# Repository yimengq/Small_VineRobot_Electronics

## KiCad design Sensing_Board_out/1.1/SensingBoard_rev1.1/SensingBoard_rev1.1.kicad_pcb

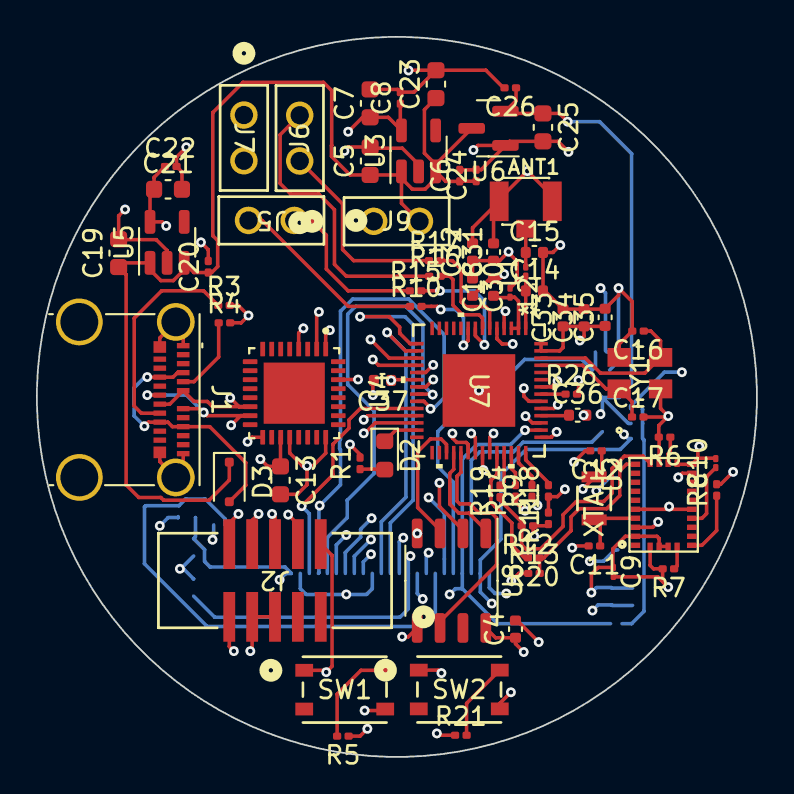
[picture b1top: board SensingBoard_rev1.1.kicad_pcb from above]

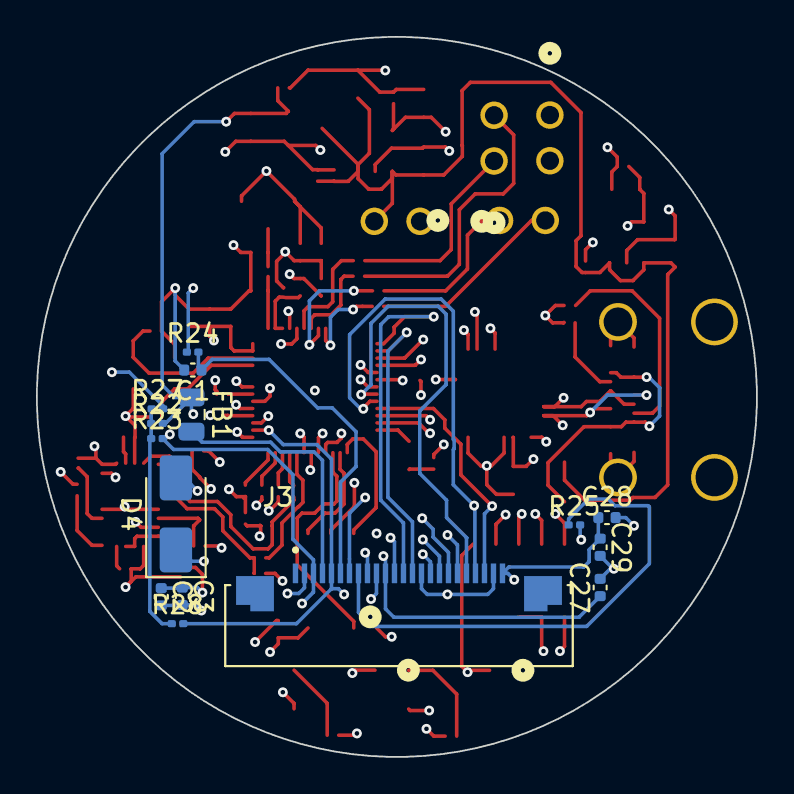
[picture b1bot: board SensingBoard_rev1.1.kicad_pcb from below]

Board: 6 copper layers, 40.0 x 40.0 mm, 89 parts (15 on the bottom side), 74 nets.

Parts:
ANT1: U.FL-R-SMT-1
C1, C2, C4, C18, C29, C30, C34, C36, C37: 100nF; C_0402_1005Metric
C3: 4.7uF; C_0402_1005Metric
C5, C7, C13, C19, C21, C23, C25: 10uF; C_0603_1608Metric
C6, C8, C20, C22, C24, C26: 1uF; C_0201_0603Metric
C9, C10: 0.1uF; C_01005_0402Metric
C11, C12: 22pF; C_0201_0603Metric
C14, C15: 1.6pF; C_0402_1005Metric
C16, C17: 18pF; C_0201_0603Metric
C27, C28, C31, C32, C33: 2.2uF; C_0402_1005Metric
C35: 10nF; C_0402_1005Metric
D2: LED; LED_0603_1608Metric
D3: PMEG6010CEJ; D_SOD-323F
D4: B140-E3; D_SMA
FB1: 120R-3A; C_0805_2012Metric
J1: USB_C_Receptacle; USB_C_Receptacle_Molex_105450-0101-L
J2: 3221-10-0300-00; CONN10_3221-10-0300-00_CNC
J3: F32R-1A7H1-11024; AMPHENOL_F32R-1A7H1-11024
J5, J6, J7, J9: RS1-02-G; CONN_RS1-02-G_ADM
L1, L2: 2nH; L_01005_0402Metric
R1: 100; R_0201_0603Metric
R3: 6.1K; R_0201_0603Metric
R4: 5.1K; R_0201_0603Metric
R5, R6, R7, R8, R11, R12, R13, R21, R24, R25: 10k; R_0201_0603Metric
R9, R10, R14, R15, R16, R17, R18, R19, R20, R22, R27: 0k; R_0201_0603Metric
R23, R28: 4.7k; R_0201_0603Metric
R26: 499; R_0201_0603Metric
SW1, SW2: PTS815 SJM 250 SMTR LFS; SW4_PTS815 SJM 250 SMTR LFS_CNK
U2: BNO055; LGA28R50P4X10_380X520X100
U3: MIC5504-3.3YM5; SOT-23-5
U4: FT232RQ; QFN50P500X500X90-33N
U5: MIC5504-1.8YM5; SOT-23-5
U6: MCP1700x-280xxTT; SOT-23
U7: ESP32-S3; QFN56_7X7_EXP
U8: GD25D05CT; SOP-8_3.9x4.9mm_P1.27mm
XTAL2: ABS07-32.768KHZ-7-T; XTAL_ABS07-32.768KHZ-7-T_ABR
Y1: ABM8G-40.000MHZ-18-D2Y-T; CRYSTAL_ABM8G_ABR

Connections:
+1V8: C21.1, C22.1, J3.10, U5.5 (VOUT)
+2V8: C25.1, C26.1, C27.1, D4.2 (A), FB1.1, J3.11, R22.2, U6.2 (VO)
+3.3V: C2.1, C3.1, C4.1, C7.1, C8.1, C9.1, C13.1, C30.1, C31.1, C32.1, C33.1, C34.1, C35.1, C36.1, C37.1, J2.5, L2.1, R1.2, R5.1, R11.1, R12.1, R13.1, R21.1, R24.1, R27.2, U2.3 (VDD), U2.4 (NBOOT_LOAD_PIN), U2.28 (VDDIO), U3.5 (VOUT), U4.1 (VCCIO), U4.19 (VCC), U7.20 (VDD3P3_RTC), U7.46 (VDD3P3_CPU), U7.55 (VDDA), U7.56 (VDDA), U8.8 (VCC)
+5V: D3.2 (A), J1.A4 (VBUS), J1.A9 (VBUS), J1.B4 (VBUS), J1.B9 (VBUS)
BNO_INT: R14.1, U2.14 (INT)
BNO_SCL: R12.2, R19.1, U2.19 (COM1)
BNO_SDA: R13.2, R20.1, U2.20 (COM0)
CAM_RESET: C1.1, J3.6, R24.2
CHIP_EN: J2.6, SW1.1, U7.4 (CHIP_PU)
D0/A0: R17.2, U7.6 (GPIO1)
D1/A1: R16.2, U7.7 (GPIO2)
D2/A2: R15.2, U7.8 (GPIO3)
D3/A3: R10.2, U7.9 (GPIO4)
DRV_FAULT: J7.1, R11.2, R18.1
DRV_SLEEP: J7.2, R9.1
GND: ANT1.GND1, ANT1.GND2, C1.2, C2.2, C3.2, C4.2, C5.2, C6.2, C7.2, C8.2, C9.2, C10.2, C11.2, C12.2, C13.2, C14.2, C15.2, C16.2, C17.2, C18.2, C19.2, C20.2, C21.2, C22.2, C23.2, C24.2, C25.2, C26.2, C27.2, C28.2, C29.2, C30.2, C31.2, C32.2, C33.2, C34.2, C35.2, C36.2, C37.2, J1.A1 (GND), J1.A12 (GND), J1.B1 (GND), J1.B12 (GND), J1.S1 (SHIELD), J2.3, J2.4, J3.2, J3.15, J3.23, J9.1, R3.2, R4.2, R6.2, R7.2, R8.2, R25.2, SW1.4, SW2.4, U2.2 (GND), U2.10 (PIN10), U2.15 (PIN15), U2.16 (PIN16), U2.18 (COM2), U2.25 (GNDIO), U3.2 (GND), U4.4 (GND), U4.17 (GND), U4.20 (GND), U4.24 (AGND), U5.2 (GND), U6.1 (GND), U7.57 (GND), U8.4 (VSS), Y1.2 (GND), Y1.4 (GND)
GPIO0: SW2.1, U7.5 (GPIO0)
GPIO33: R20.2, U7.38 (GPIO33)
GPIO34: R19.2, U7.39 (GPIO34)
GPIO35: R14.2, U7.40 (GPIO35)
GPIO36: R9.2, U7.41 (GPIO36)
GPIO37: R18.2, U7.42 (GPIO37)
IO10/XMCLK: J3.13, U7.15 (GPIO10)
IO11/DVP_Y8: J3.14, U7.16 (GPIO11)
IO12/DVP_Y7: J3.16, U7.17 (GPIO12)
IO13/DVP_PCLK: J3.17, U7.18 (GPIO13)
IO14/DVP_Y6: J3.18, U7.19 (GPIO14)
IO15/DVP_Y2: J3.19, U7.21 (XTAL_32K_P)
IO16/DVP_Y5: J3.20, U7.22 (XTAL_32K_N)
IO17/DVP_Y3: J3.21, U7.23 (GPIO17)
IO18/DVP_Y4: J3.22, U7.24 (GPIO18)
IO21/USER_LED: D2.1 (K), U7.27 (GPIO21)
IO38/DVP_VSYNC: J3.7, U7.43 (GPIO38)
IO47/DVP_HREF: J3.9, U7.37 (SPICLK_P)
IO48/DVP_Y9: J3.12, U7.36 (SPICLK_N)
MOTOR1_AIN1: J5.2, R10.1
MOTOR1_AIN2: J5.1, R15.1
MOTOR2_BIN1: J6.2, R16.1
MOTOR2_BIN2: J6.1, R17.1
MTCK/IO39/CAM_SCL: J2.7, J3.5, R28.2, U7.44 (MTCK)
MTDI/IO41/PDM_DATA: J2.9, U7.47 (MTDI)
MTDO/IO40/CAM_SDA: J2.8, J3.3, R23.2, U7.45 (MTDO)
MTMS/IO42/PDM_CLK: J2.10, U7.48 (MTMS)
unnamed: ANT1.SIG, C15.1, L1.2
unnamed: C18.1, L2.2, U7.2 (VDD3P3), U7.3 (VDD3P3)
unnamed: D2.2 (A), R1.1
unnamed: C28.1, C29.1, D4.1 (K), J3.24
unnamed: FB1.2, J3.4
unnamed: J1.A5 (CC1), R4.1
unnamed: J1.B5 (CC2), R3.1
unnamed: J3.8, R25.1
unnamed: R5.2, SW1.2
unnamed: R21.2, SW2.2
unnamed: R22.1, R23.1, R27.1, R28.1
unnamed: C10.1, U2.9 (CAP)
unnamed: R6.1, U2.17 (COM3)
unnamed: R8.1, U2.6 (PS0)
unnamed: R7.1, U2.5 (PS1)
unnamed: C12.1, U2.27 (XIN32), XTAL2.2
unnamed: C11.1, U2.26 (XOUT32), XTAL2.1
unnamed: C14.1, L1.1, U7.1 (LNA_IN)
unnamed: R26.1, U7.49 (U0TXD)
unnamed: C17.1, U7.53 (XTAL_N), Y1.1
unnamed: C16.1, U7.54 (XTAL_P), Y1.3
RX_D7: U4.30 (TXD), U7.50 (U0RXD)
SPICLK: U7.33 (SPICLK), U8.6 (SCLK)
SPICS0: U7.32 (SPICS0), U8.1 (~CS)
SPID: U7.35 (SPID), U8.5 (SI/IO0)
SPIQ: U7.34 (SPIQ), U8.2 (O1/SO)
SPIWP: U7.31 (SPIWP), U8.3 (~WP)
TX_D6: R26.2, U4.2 (RXD)
USB_DN: J1.A7 (D-), J1.B7 (D-), U4.15 (USBDM), U7.25 (GPIO19)
USB_DP: J1.A6 (D+), J1.B6 (D+), U4.14 (USBDP), U7.26 (GPIO20)
VDC: C5.1, C6.1, C19.1, C20.1, C23.1, C24.1, D3.1 (K), J9.2, U3.1 (VIN), U3.3 (EN), U5.1 (VIN), U5.3 (EN), U6.3 (VI)
